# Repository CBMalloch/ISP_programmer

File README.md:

ISP_programmer
==============

Atmel programmer with ICSP/ISP header and ZIF socket

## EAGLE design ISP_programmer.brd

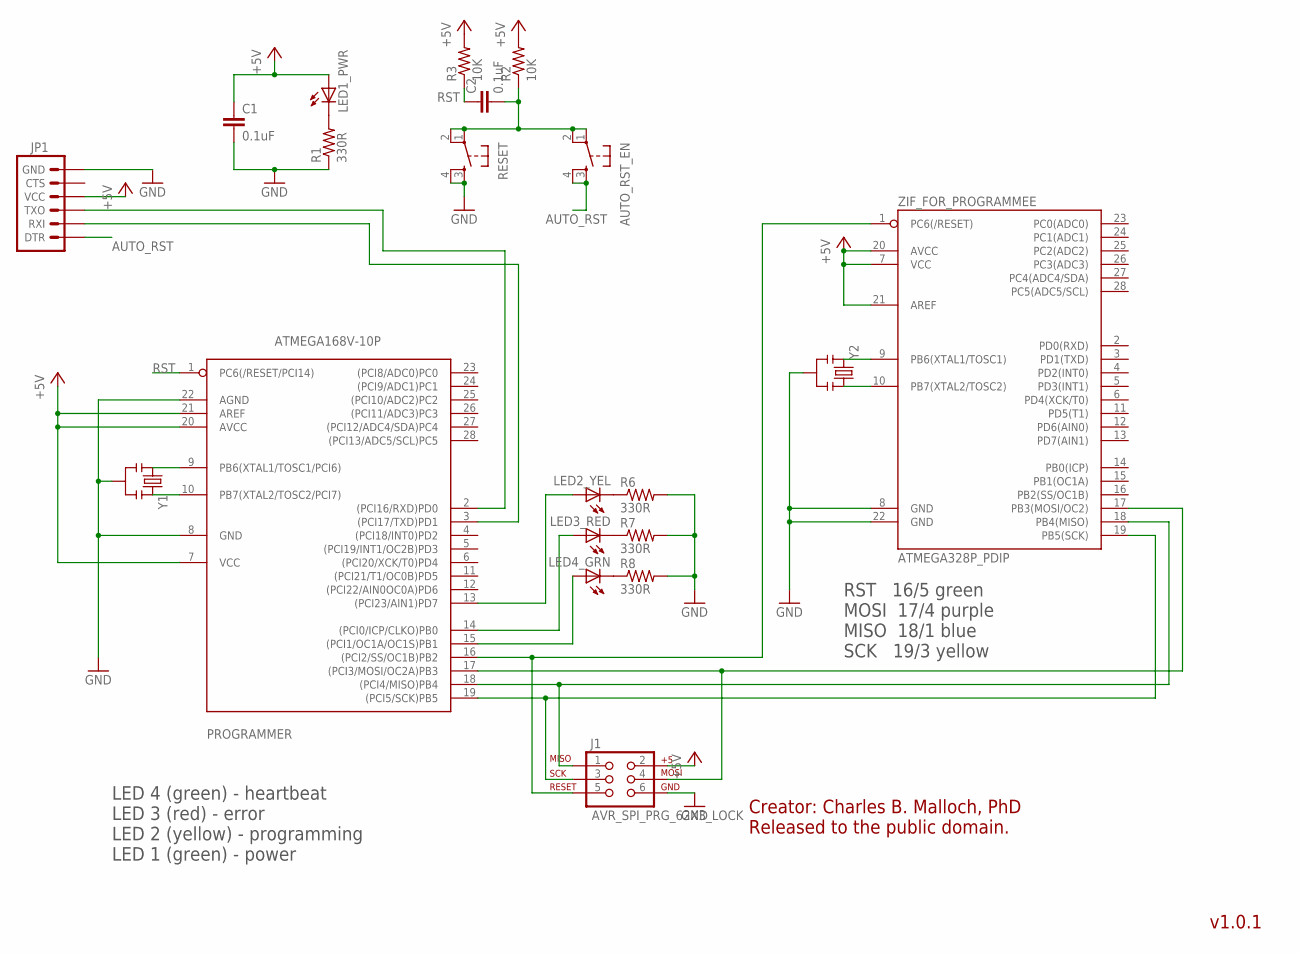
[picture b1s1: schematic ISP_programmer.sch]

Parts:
AUTO_RST_EN: TAC_SWITCHPTH; TACTILE-PTH
C1, C2: 0.1uF; CAP-PTH-SMALLEZ
J1: AVR_SPI_PRG_62X3_LOCK; 2X3_LOCK
JP1: ARDUINO_SERIAL_PROGRAMLOCK; 1X06_LOCK
LED1_PWR, LED2_YEL, LED3_RED, LED4_GRN: LED3MM
PROGRAMMER: ATMEGA168V-10P; DIL28-3
R1, R6, R7, R8: 330R; 0204/7
R2, R3: 10K; 0204/7
RESET: TAC_SWITCHPTH; TACTILE-PTH
Y1, Y2: RESONATORPTH; RESONATOR-PTH
ZIF_FOR_PROGRAMMEE: ATMEGA328P_PDIP; DIL28-3

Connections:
+5V: C1.1, J1.2, JP1.4 (VCC), LED1_PWR.A, PROGRAMMER.7 (VCC), PROGRAMMER.20 (AVCC), PROGRAMMER.21 (AREF), R2.2, R3.2, ZIF_FOR_PROGRAMMEE.7 (VCC), ZIF_FOR_PROGRAMMEE.20 (AVCC), ZIF_FOR_PROGRAMMEE.21 (AREF)
AUTO_RST: AUTO_RST_EN.3, AUTO_RST_EN.4, JP1.1 (DTR)
GND: C1.2, J1.6, JP1.6 (GND), PROGRAMMER.8 (GND), PROGRAMMER.22 (AGND), R1.1, R6.2, R7.2, R8.2, RESET.3, RESET.4, Y1.2, Y2.2, ZIF_FOR_PROGRAMMEE.8 (GND), ZIF_FOR_PROGRAMMEE.22 (GND)
unnamed: Y2.1, ZIF_FOR_PROGRAMMEE.10 (PB7(XTAL2/TOSC2))
unnamed: LED1_PWR.K (C), R1.2
unnamed: PROGRAMMER.9 (PB6(XTAL1/TOSC1/PCI6)), Y1.1
unnamed: JP1.3 (TXO), PROGRAMMER.2 ((PCI16/RXD)PD0)
unnamed: JP1.2 (RXI), PROGRAMMER.3 ((PCI17/TXD)PD1)
unnamed: AUTO_RST_EN.1, AUTO_RST_EN.2, C2.2, R2.1, RESET.1, RESET.2
unnamed: Y2.3, ZIF_FOR_PROGRAMMEE.9 (PB6(XTAL1/TOSC1))
unnamed: LED2_YEL.K (C), R6.1
unnamed: PROGRAMMER.10 (PB7(XTAL2/TOSC2/PCI7)), Y1.3
unnamed: J1.3, PROGRAMMER.19 ((PCI5/SCK)PB5), ZIF_FOR_PROGRAMMEE.19 (PB5(SCK))
unnamed: J1.1, PROGRAMMER.18 ((PCI4/MISO)PB4), ZIF_FOR_PROGRAMMEE.18 (PB4(MISO))
unnamed: J1.4, PROGRAMMER.17 ((PCI3/MOSI/OC2A)PB3), ZIF_FOR_PROGRAMMEE.17 (PB3(MOSI/OC2))
unnamed: J1.5, PROGRAMMER.16 ((PCI2/SS/OC1B)PB2), ZIF_FOR_PROGRAMMEE.1 (PC6(/RESET))
unnamed: LED3_RED.K (C), R7.1
unnamed: LED4_GRN.K (C), R8.1
unnamed: LED2_YEL.A, PROGRAMMER.13 ((PCI23/AIN1)PD7)
unnamed: LED3_RED.A, PROGRAMMER.14 ((PCI0/ICP/CLKO)PB0)
unnamed: LED4_GRN.A, PROGRAMMER.15 ((PCI1/OC1A/OC1S)PB1)
RST: C2.1, PROGRAMMER.1 (PC6(/RESET/PCI14)), R3.1

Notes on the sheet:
v1.0.1
Creator: Charles B. Malloch, PhD Released to the public domain.
LED 4 (green) - heartbeat LED 3 (red) - error LED 2 (yellow) - programming LED 1 (green) - power
RST 16/5 green MOSI 17/4 purple MISO 18/1 blue SCK 19/3 yellow

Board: 2 copper layers, 20 parts (0 on the bottom side), 22 nets, no tracks yet.

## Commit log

2013-12-15 Created schematic and did a board layout of the components without routing
    Enough to solder a breadboard with a ZIF socket and a 2x3 ICSP/ISP
    header
2013-12-16 trying to do first commit

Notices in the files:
ISP_programmer.brd:
released to public domain
parts and their libraries:
SparkFun-FreqCtrl: Licensing: CC v3.0 Share-Alike You are welcome to use this library for commercial purposes.
